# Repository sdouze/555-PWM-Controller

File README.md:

This is 555 PWM Controller that is made to control a 12v Fan

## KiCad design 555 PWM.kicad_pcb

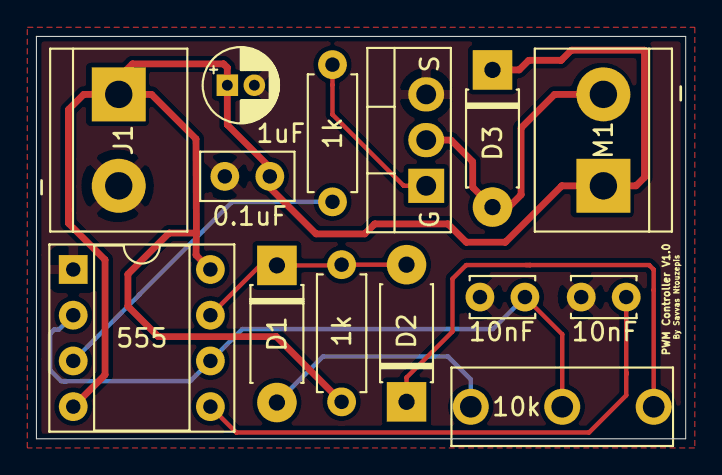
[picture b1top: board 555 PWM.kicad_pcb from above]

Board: 2 copper layers, 36.1 x 22.4 mm, 14 parts (0 on the bottom side), 10 nets.

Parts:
0.1uF: 0.1uF; C_Disc_D5.0mm_W2.5mm_P2.50mm
1k, 1k#2: 1k; R_Axial_DIN0207_L6.3mm_D2.5mm_P7.62mm_Horizontal
1uF: 1uF; CP_Radial_D4.0mm_P1.50mm
10k: 10k; B10k
10nF, 10nF#2: 10nf; C_Disc_D3.4mm_W2.1mm_P2.50mm
555: NE555; DIP-8_W7.62mm_Socket
D1, D2, D3: 1N4002; D_DO-41_SOD81_P7.62mm_Horizontal
J1: Screw_Terminal_01x02; TerminalBlock_bornier-2_P5.08mm
M1: Motor_DC; TerminalBlock_bornier-2_P5.08mm
Q2: IRFZ44; TO-220-3_Vertical

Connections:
+12V: 0.1uF.2, 1k.1, 1uF.1, 555.4, 555.8, D3.1, J1.1, M1.1
Earth: 0.1uF.1, 1uF.2, 10nF.2, 10nF#2.2, 555.1, J1.2, Q2.3
unnamed: 10k.2, 10nF.1, 555.2, 555.6
unnamed: 10nF#2.1, 555.5
unnamed: 1k.2, 555.7, D1.1, D2.2
unnamed: 10k.3, D1.2
unnamed: 10k.1, D2.1
unnamed: D3.2, M1.2, Q2.2
unnamed: 1k#2.2, Q2.1
OUT: 1k#2.1, 555.3

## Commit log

2020-03-16 schematic pcb files
2020-03-16 readme
